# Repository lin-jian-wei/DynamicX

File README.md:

# DynamicX
This repository is about DynamicX

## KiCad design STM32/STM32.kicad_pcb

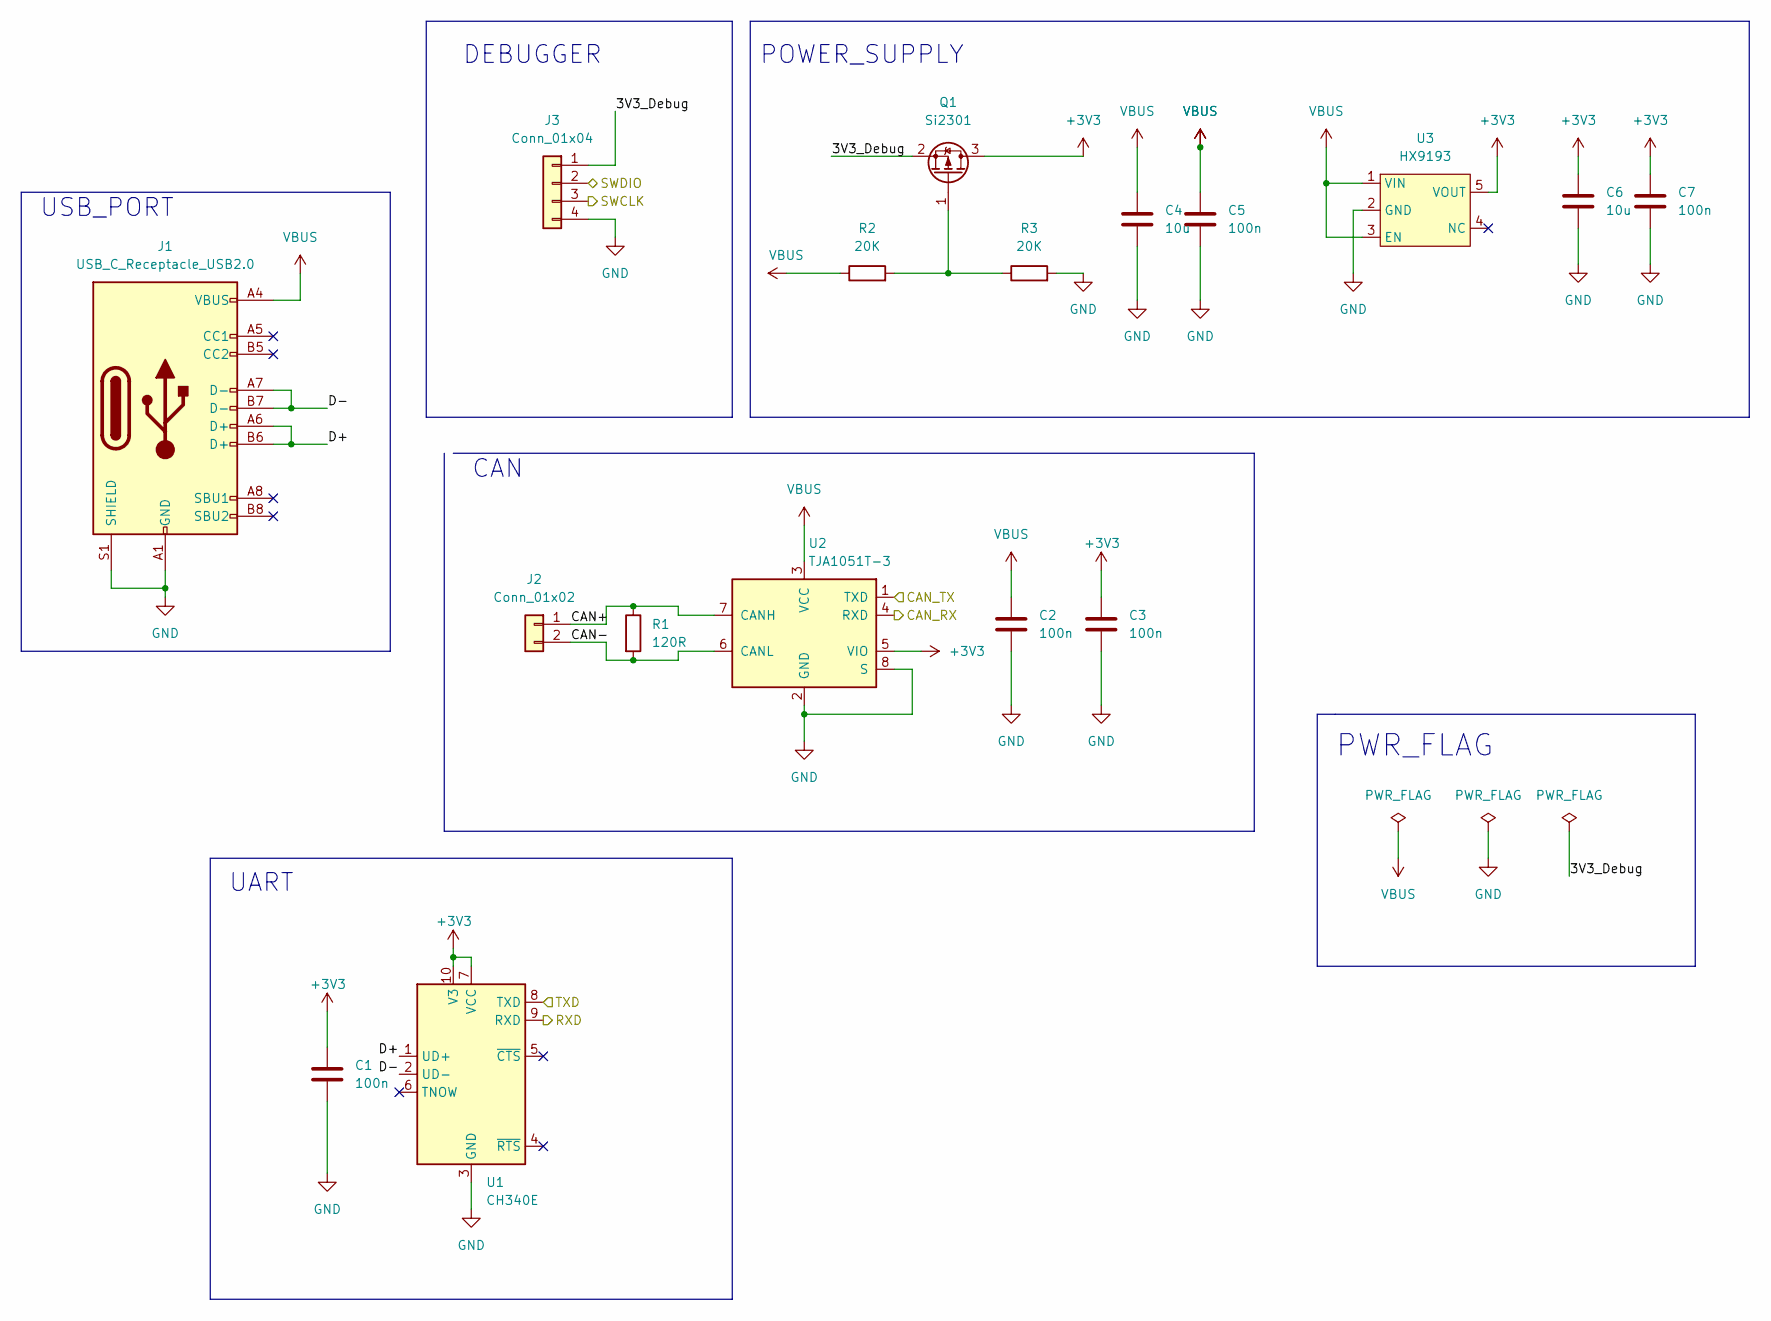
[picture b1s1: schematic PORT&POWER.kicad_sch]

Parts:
C1, C2, C3, C5, C7: 100n; C_0603_1608Metric
C4, C6: 10u; C_0603_1608Metric
J1: USB_C_Receptacle_USB2.0; USB_C_Receptacle_HRO_TYPE-C-31-M-12
J2: Conn_01x02; JST_GH_SM02B-GHS-TB_1x02-1MP_P1.25mm_Horizontal
J3: Conn_01x04; PinHeader_1x04_P2.54mm_Vertical
Q1: Si2301; TSOT-23
R1: 120R; R_0603_1608Metric
R2, R3: 20K; R_0603_1608Metric
U1: CH340E; MSOP-10_3x3mm_P0.5mm
U2: TJA1051T-3; SOIC-8_3.9x4.9mm_P1.27mm
U3: HX9193; SOT-23-5_HandSoldering

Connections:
+3V3: C1.1, C3.1, C6.1, C7.1, Q1.3 (D), U1.7 (VCC), U1.10 (V3), U2.5 (VIO), U3.5 (VOUT); also elsewhere on the board
/PORT&POWER/3V3_Debug: J3.1, Q1.2 (S)
/PORT&POWER/CAN+: J2.1, R1.1, U2.7 (CANH)
/PORT&POWER/CAN-: J2.2, R1.2, U2.6 (CANL)
/PORT&POWER/D+: J1.A6 (D+), J1.B6 (D+), U1.1 (UD+)
/PORT&POWER/D-: J1.A7 (D-), J1.B7 (D-), U1.2 (UD-)
/STM32_MinimumSystem/PA9: U1.9 (RXD); also elsewhere on the board
/STM32_MinimumSystem/PA10: U1.8 (TXD); also elsewhere on the board
/STM32_MinimumSystem/PA11: U2.4 (RXD); also elsewhere on the board
/STM32_MinimumSystem/PA12: U2.1 (TXD); also elsewhere on the board
/STM32_MinimumSystem/PA13: J3.2; also elsewhere on the board
/STM32_MinimumSystem/PA14: J3.3; also elsewhere on the board
GND: C1.2, C2.2, C3.2, C4.2, C5.2, C6.2, C7.2, J1.A1 (GND), J1.A12 (GND), J1.B1 (GND), J1.B12 (GND), J1.S1 (SHIELD), J3.4, R3.2, U1.3 (GND), U2.2 (GND), U2.8 (S), U3.2 (GND); also elsewhere on the board
unnamed: Q1.1 (G), R2.2, R3.1
VBUS: C2.1, C4.1, C5.1, J1.A4 (VBUS), J1.A9 (VBUS), J1.B4 (VBUS), J1.B9 (VBUS), R2.1, U2.3 (VCC), U3.1 (VIN), U3.3 (EN); also elsewhere on the board

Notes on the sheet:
PWR_FLAG
USB_PORT
UART
DEBUGGER
POWER_SUPPLY
CAN

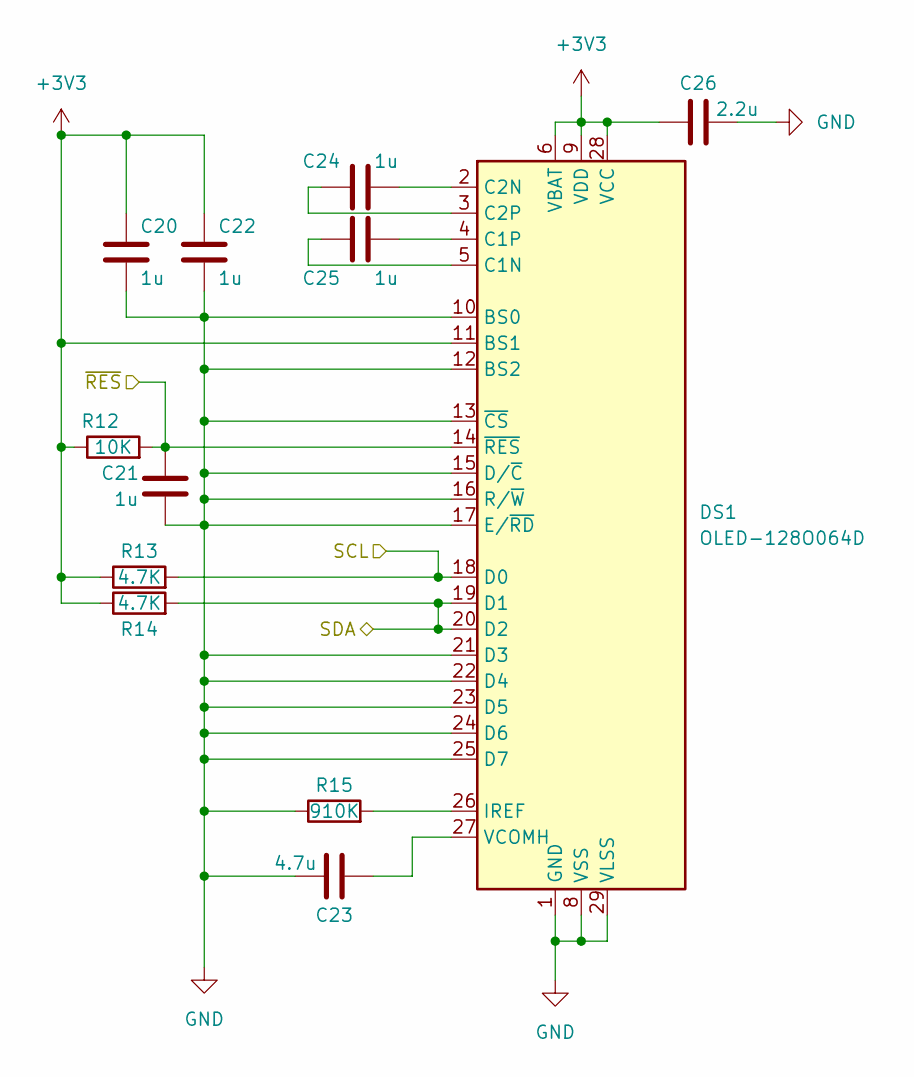
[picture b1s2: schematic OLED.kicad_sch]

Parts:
C20, C21, C22, C24, C25: 1u; C_0603_1608Metric
C23: 4.7u; C_0603_1608Metric
C26: 2.2u; C_0603_1608Metric
DS1: OLED-128O064D; OLED
R12: 10K; R_0603_1608Metric
R13, R14: 4.7K; R_0603_1608Metric
R15: 910K; R_0603_1608Metric

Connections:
+3V3: C20.1, C22.1, C26.2, DS1.6 (VBAT), DS1.9 (VDD), DS1.11 (BS1), DS1.28 (VCC), R12.1, R13.1, R14.1; also elsewhere on the board
/STM32_MinimumSystem/PB5: C21.1, DS1.14 (~RES), R12.2; also elsewhere on the board
/STM32_MinimumSystem/PB6: DS1.18 (D0), R13.2; also elsewhere on the board
/STM32_MinimumSystem/PB7: DS1.19 (D1), DS1.20 (D2), R14.2; also elsewhere on the board
GND: C20.2, C21.2, C22.2, C23.1, C26.1, DS1.1 (GND), DS1.8 (VSS), DS1.10 (BS0), DS1.12 (BS2), DS1.13 (~CS), DS1.15 (D/~C), DS1.16 (R/~W), DS1.17 (E/~RD), DS1.21 (D3), DS1.22 (D4), DS1.23 (D5), DS1.24 (D6), DS1.25 (D7), DS1.29 (VLSS), DS1.30 (GND), R15.1; also elsewhere on the board
unnamed: C23.2, DS1.27 (VCOMH)
unnamed: C24.1, DS1.2 (C2N)
unnamed: C24.2, DS1.3 (C2P)
unnamed: C25.1, DS1.4 (C1P)
unnamed: C25.2, DS1.5 (C1N)
unnamed: DS1.26 (IREF), R15.2

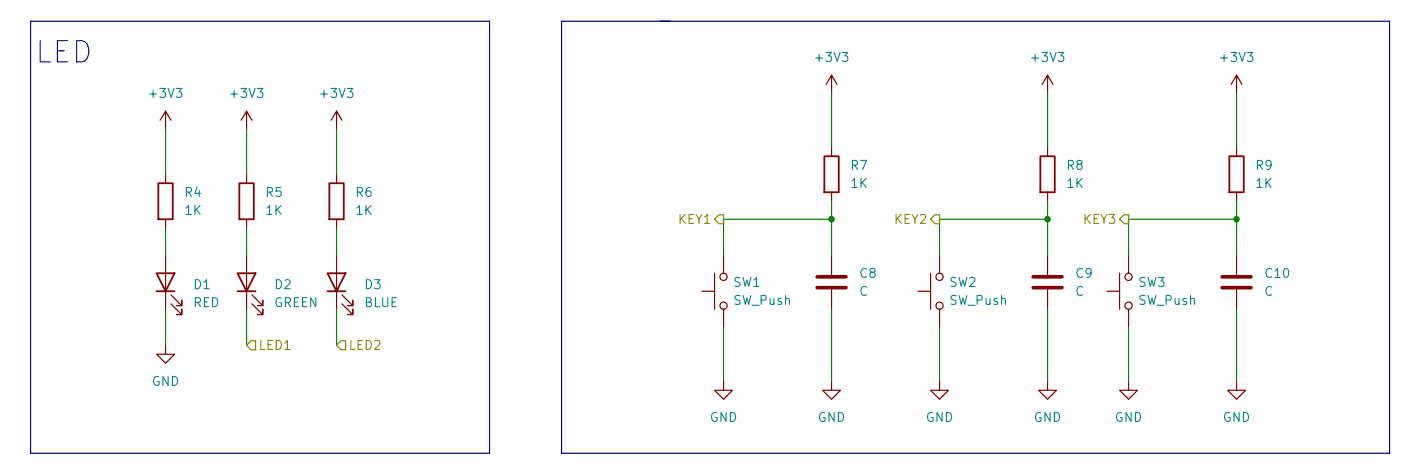
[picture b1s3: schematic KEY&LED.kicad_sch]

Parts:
C8, C9, C10: C; C_0603_1608Metric
D1: RED; LED_0603_1608Metric
D2: GREEN; LED_0603_1608Metric
D3: BLUE; LED_0603_1608Metric
R4, R5, R6, R7, R8, R9: 1K; R_0603_1608Metric
SW1, SW2, SW3: SW_Push; SW_Push_1P1T_NO_6x6mm_H9.5mm

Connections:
+3V3: R4.1, R5.1, R6.1, R7.1, R8.1, R9.1; also elsewhere on the board
/STM32_MinimumSystem/PA15: D2.1 (K); also elsewhere on the board
/STM32_MinimumSystem/PB3: D3.1 (K); also elsewhere on the board
/STM32_MinimumSystem/PB4: C8.1, R7.2, SW1.2; also elsewhere on the board
/STM32_MinimumSystem/PB8: C9.1, R8.2, SW2.2; also elsewhere on the board
/STM32_MinimumSystem/PB9: C10.1, R9.2, SW3.2; also elsewhere on the board
GND: C8.2, C9.2, C10.2, D1.1 (K), SW1.1, SW2.1, SW3.1; also elsewhere on the board
unnamed: D1.2 (A), R4.2
unnamed: D2.2 (A), R5.2
unnamed: D3.2 (A), R6.2

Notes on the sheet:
LED

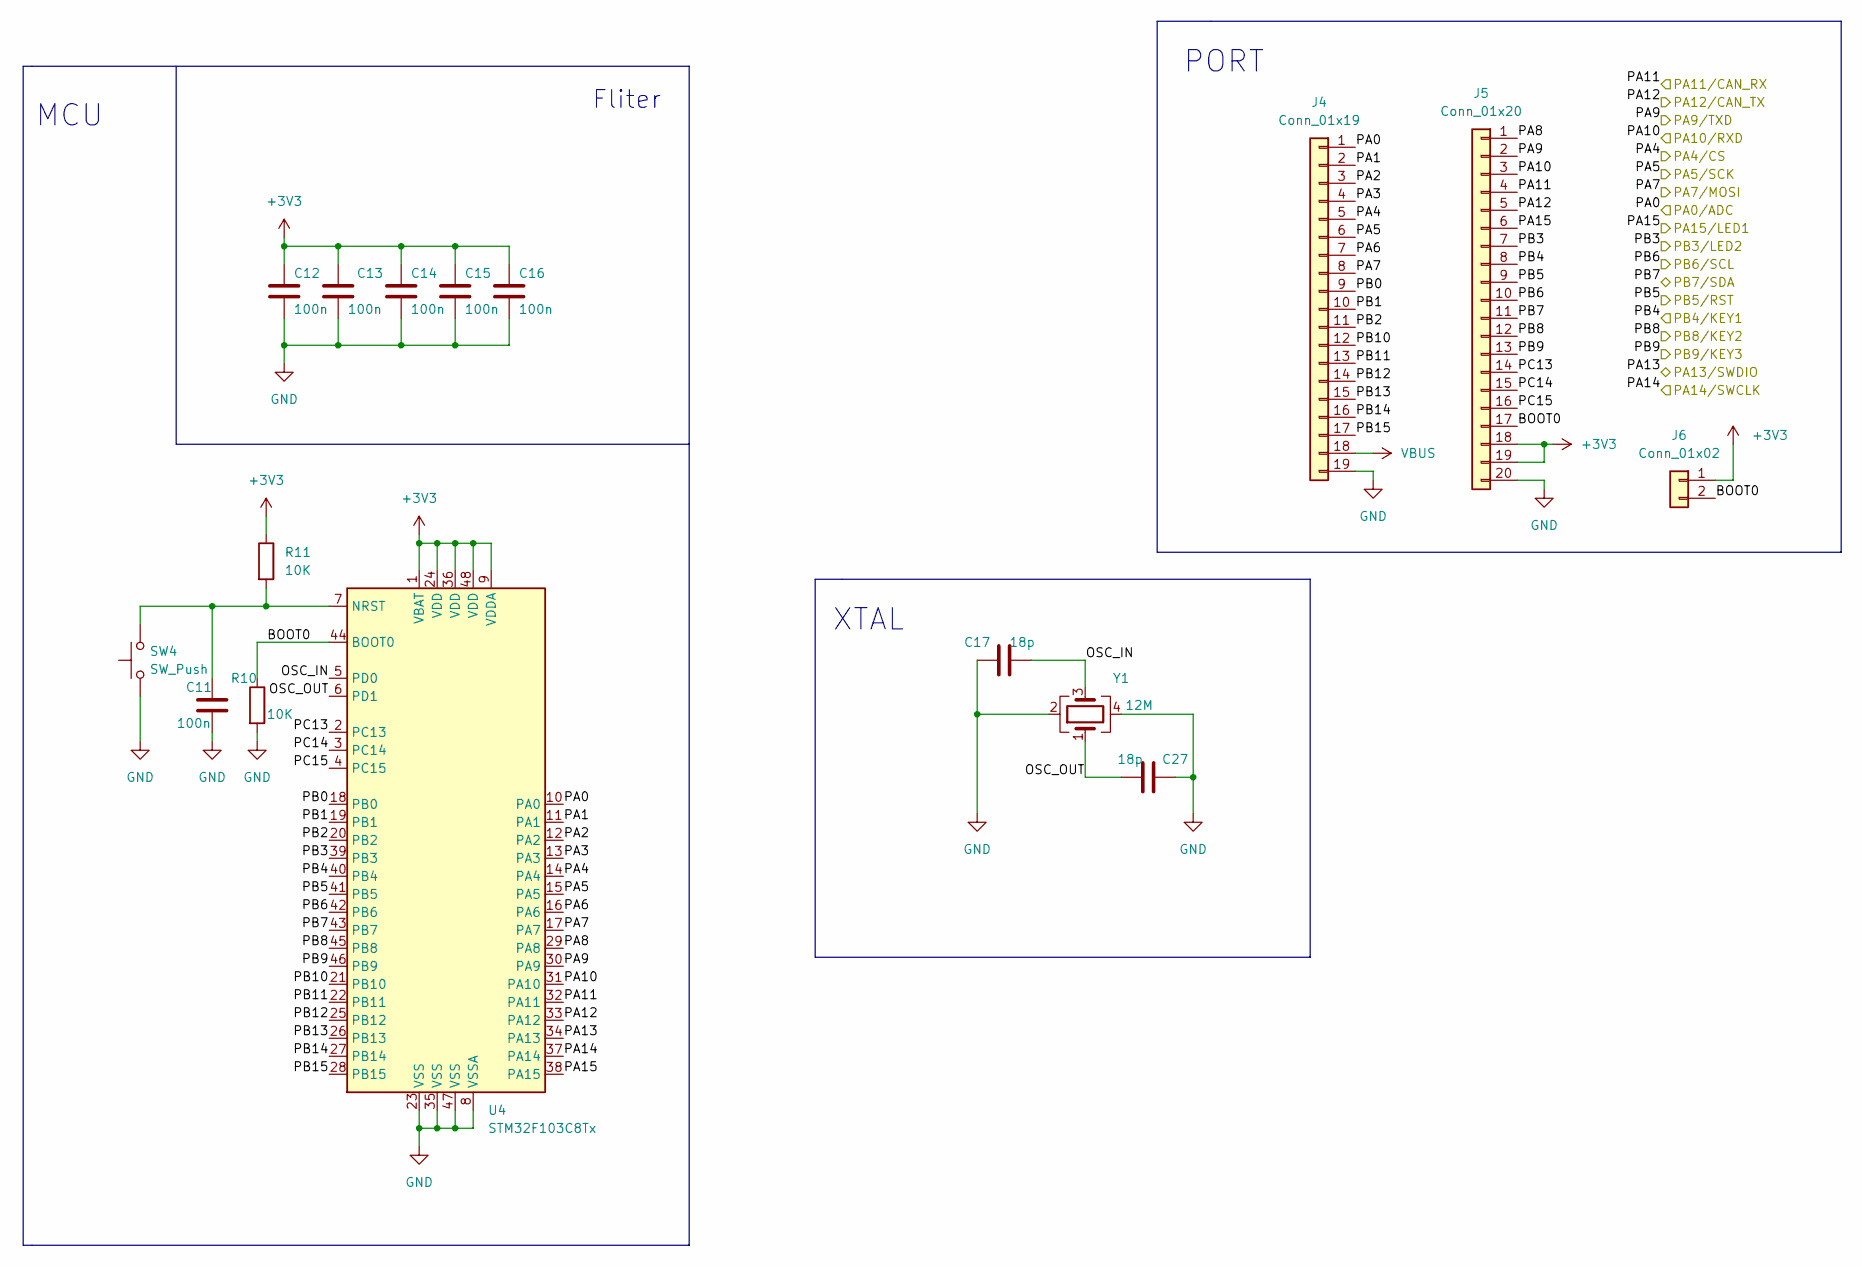
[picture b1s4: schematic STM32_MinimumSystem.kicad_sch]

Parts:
C11, C12, C13, C14, C15, C16: 100n; C_0603_1608Metric
C17, C27: 18p; C_0603_1608Metric
J4: Conn_01x19; PinHeader_1x19_P2.54mm_Vertical
J5: Conn_01x20; PinHeader_1x20_P2.54mm_Vertical
J6: Conn_01x02; PinHeader_1x02_P2.54mm_Vertical
R10, R11: 10K; R_0603_1608Metric
SW4: SW_Push; SW_Push_1P1T_NO_6x6mm_H9.5mm
U4: STM32F103C8Tx; LQFP-48_7x7mm_P0.5mm
Y1: 12M; Crystal_SMD_3225-4Pin_3.2x2.5mm

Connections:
+3V3: C12.1, C13.1, C14.1, C15.1, C16.1, J5.18, J5.19, J6.1, R11.1, U4.1 (VBAT), U4.9 (VDDA), U4.24 (VDD), U4.36 (VDD), U4.48 (VDD); also elsewhere on the board
/STM32_MinimumSystem/BOOT0: J5.17, J6.2, R10.1, U4.44 (BOOT0)
/STM32_MinimumSystem/OSC_IN: C17.2, U4.5 (PD0), Y1.3
/STM32_MinimumSystem/OSC_OUT: C27.1, U4.6 (PD1), Y1.1
/STM32_MinimumSystem/PA0: J4.1, U4.10 (PA0); also elsewhere on the board
/STM32_MinimumSystem/PA1: J4.2, U4.11 (PA1)
/STM32_MinimumSystem/PA2: J4.3, U4.12 (PA2)
/STM32_MinimumSystem/PA3: J4.4, U4.13 (PA3)
/STM32_MinimumSystem/PA4: J4.5, U4.14 (PA4); also elsewhere on the board
/STM32_MinimumSystem/PA5: J4.6, U4.15 (PA5); also elsewhere on the board
/STM32_MinimumSystem/PA6: J4.7, U4.16 (PA6)
/STM32_MinimumSystem/PA7: J4.8, U4.17 (PA7); also elsewhere on the board
/STM32_MinimumSystem/PA8: J5.1, U4.29 (PA8)
/STM32_MinimumSystem/PA9: J5.2, U4.30 (PA9); also elsewhere on the board
/STM32_MinimumSystem/PA10: J5.3, U4.31 (PA10); also elsewhere on the board
/STM32_MinimumSystem/PA11: J5.4, U4.32 (PA11); also elsewhere on the board
/STM32_MinimumSystem/PA12: J5.5, U4.33 (PA12); also elsewhere on the board
/STM32_MinimumSystem/PA13: U4.34 (PA13); also elsewhere on the board
/STM32_MinimumSystem/PA14: U4.37 (PA14); also elsewhere on the board
/STM32_MinimumSystem/PA15: J5.6, U4.38 (PA15); also elsewhere on the board
/STM32_MinimumSystem/PB0: J4.9, U4.18 (PB0)
/STM32_MinimumSystem/PB1: J4.10, U4.19 (PB1)
/STM32_MinimumSystem/PB2: J4.11, U4.20 (PB2)
/STM32_MinimumSystem/PB3: J5.7, U4.39 (PB3); also elsewhere on the board
/STM32_MinimumSystem/PB4: J5.8, U4.40 (PB4); also elsewhere on the board
/STM32_MinimumSystem/PB5: J5.9, U4.41 (PB5); also elsewhere on the board
/STM32_MinimumSystem/PB6: J5.10, U4.42 (PB6); also elsewhere on the board
/STM32_MinimumSystem/PB7: J5.11, U4.43 (PB7); also elsewhere on the board
/STM32_MinimumSystem/PB8: J5.12, U4.45 (PB8); also elsewhere on the board
/STM32_MinimumSystem/PB9: J5.13, U4.46 (PB9); also elsewhere on the board
/STM32_MinimumSystem/PB10: J4.12, U4.21 (PB10)
/STM32_MinimumSystem/PB11: J4.13, U4.22 (PB11)
/STM32_MinimumSystem/PB12: J4.14, U4.25 (PB12)
/STM32_MinimumSystem/PB13: J4.15, U4.26 (PB13)
/STM32_MinimumSystem/PB14: J4.16, U4.27 (PB14)
/STM32_MinimumSystem/PB15: J4.17, U4.28 (PB15)
/STM32_MinimumSystem/PC13: J5.14, U4.2 (PC13)
/STM32_MinimumSystem/PC14: J5.15, U4.3 (PC14)
/STM32_MinimumSystem/PC15: J5.16, U4.4 (PC15)
GND: C11.2, C12.2, C13.2, C14.2, C15.2, C16.2, C17.1, C27.2, J4.19, J5.20, R10.2, SW4.1, U4.8 (VSSA), U4.23 (VSS), U4.35 (VSS), U4.47 (VSS), Y1.2, Y1.4; also elsewhere on the board
unnamed: C11.1, R11.2, SW4.2, U4.7 (NRST)
VBUS: J4.18; also elsewhere on the board

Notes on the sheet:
Fliter
MCU
XTAL
PORT

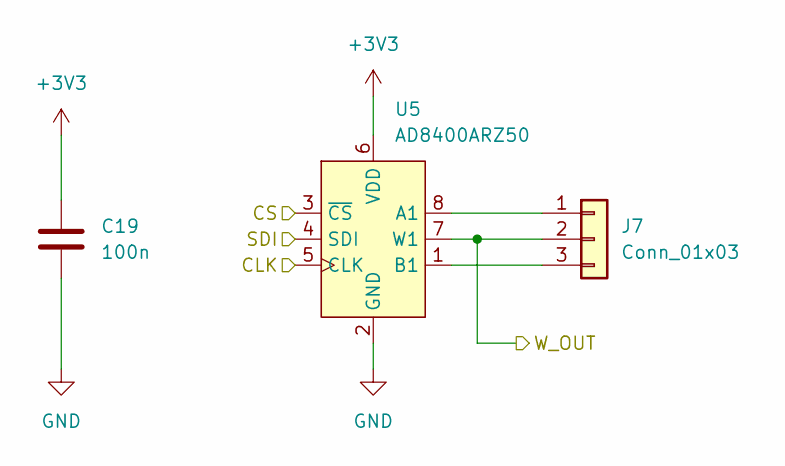
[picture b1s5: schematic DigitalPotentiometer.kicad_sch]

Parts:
C19: 100n; C_0603_1608Metric
J7: Conn_01x03; PinHeader_1x03_P2.54mm_Vertical
U5: AD8400ARZ50; SOP-8_3.9x4.9mm_P1.27mm

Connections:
+3V3: C19.1, U5.6 (VDD); also elsewhere on the board
/STM32_MinimumSystem/PA0: J7.2, U5.7 (W1); also elsewhere on the board
/STM32_MinimumSystem/PA4: U5.3 (~CS); also elsewhere on the board
/STM32_MinimumSystem/PA5: U5.5 (CLK); also elsewhere on the board
/STM32_MinimumSystem/PA7: U5.4 (SDI); also elsewhere on the board
GND: C19.2, U5.2 (GND); also elsewhere on the board
unnamed: J7.1, U5.8 (A1)
unnamed: J7.3, U5.1 (B1)

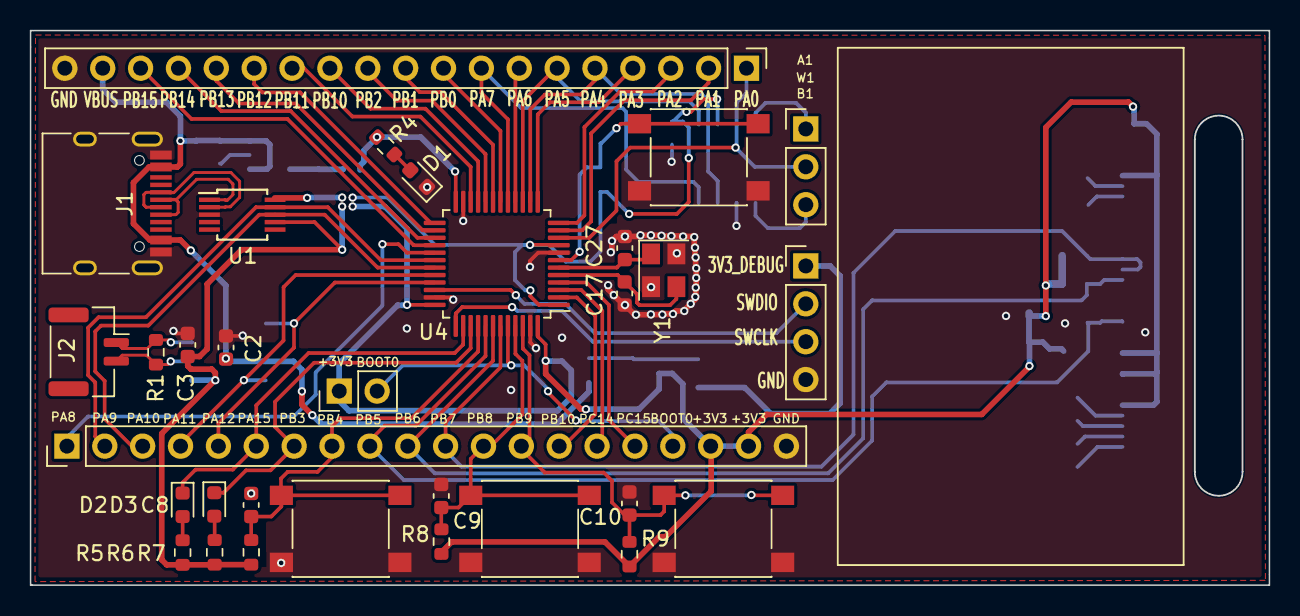
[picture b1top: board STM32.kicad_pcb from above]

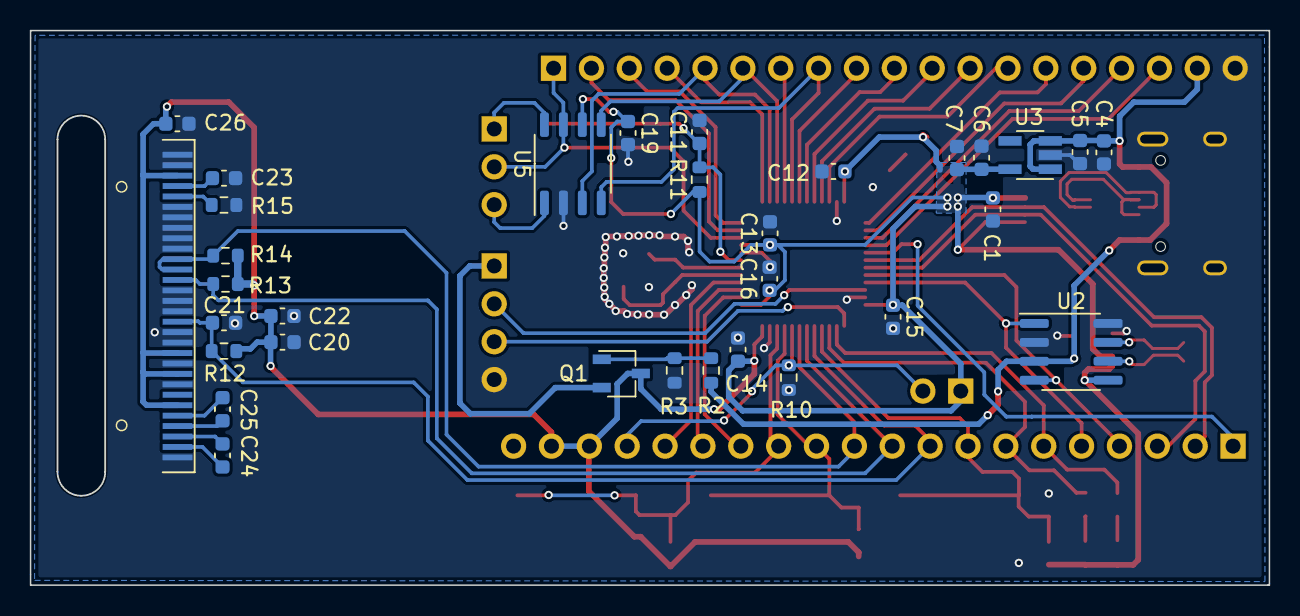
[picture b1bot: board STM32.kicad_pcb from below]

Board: 2 copper layers, 83.1 x 37.2 mm, 63 parts (31 on the bottom side), 59 nets.

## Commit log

2022-10-09 add test file
2022-10-09 STM32MiniSys
2022-10-14 更新PCB
2022-10-14 PCB更新
